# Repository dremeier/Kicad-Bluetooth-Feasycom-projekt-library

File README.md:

# Kicad-Bluetooth-Feasycom-projekt-library
KiCad 7 Library for the FSC-BT1026 Module and schematic with FSC-BT1026 and PCM5102.
The Feasycom module is a fantastic choice!
It is easy to control via UART, I2C and has I2S Audio bus as well direct SPDIF per default so no deep programming is necessary.
The Documentation is perfect and you can have a cheap experimental Board in Arduino-UNO format.

hope it is usefull for someone, 
enjoiy!

[Example Bluetooth schematic](https://github.com/dremeier/Kicad-Bluetooth-Feasycom-projekt-library/blob/main/Bluetooth_FSC-BT1026x_project/Documents/Bluetooth_PCM5102_Circuit.pdf)
<object data="https://github.com/dremeier/Kicad-Bluetooth-Feasycom-projekt-library/blob/main/Bluetooth_FSC-BT1026x_project/Documents/Bluetooth_PCM5102_Circuit.pdf" type="application/pdf" width="100%">
</object>

## KiCad 3D-Package

## KiCad Projekt with the Feasycom Bluetooth Module (BMW-IbusTrx-Teensy)

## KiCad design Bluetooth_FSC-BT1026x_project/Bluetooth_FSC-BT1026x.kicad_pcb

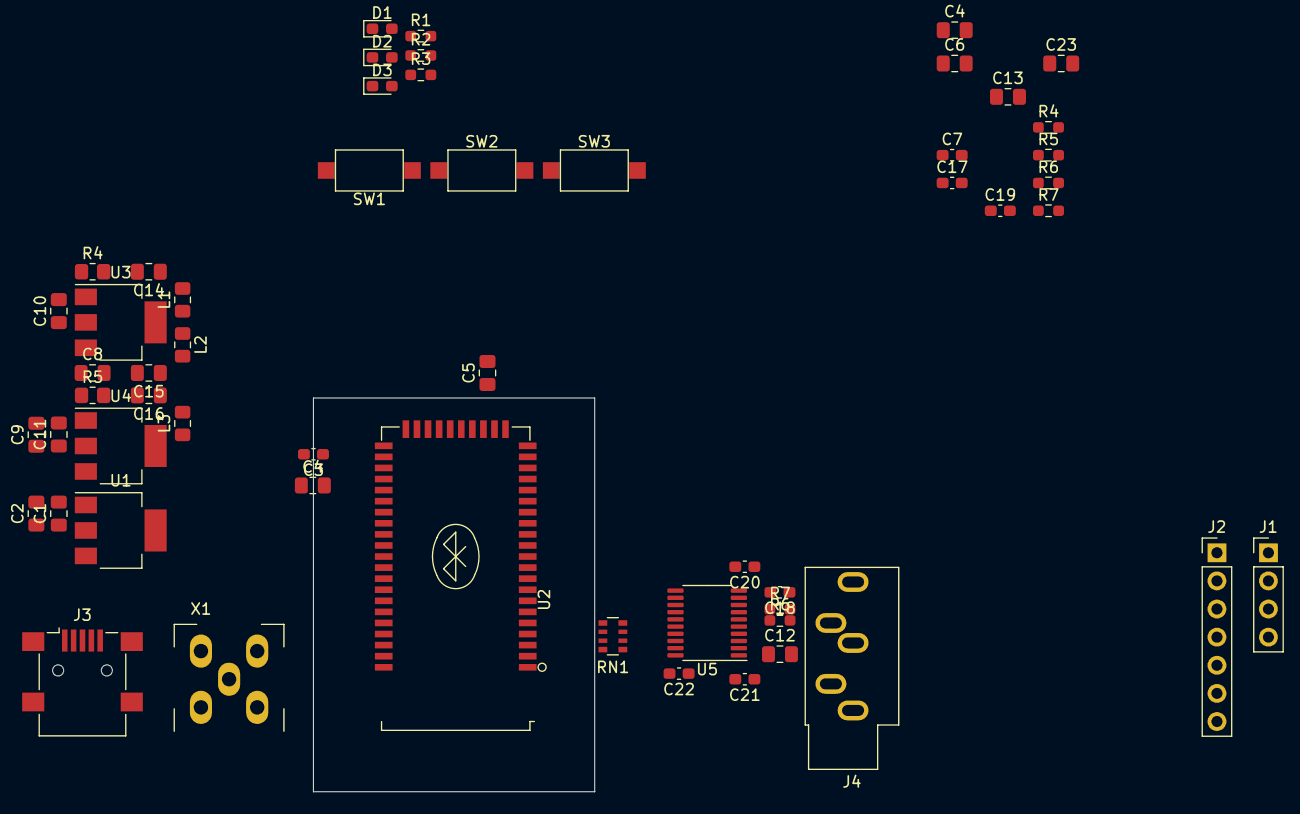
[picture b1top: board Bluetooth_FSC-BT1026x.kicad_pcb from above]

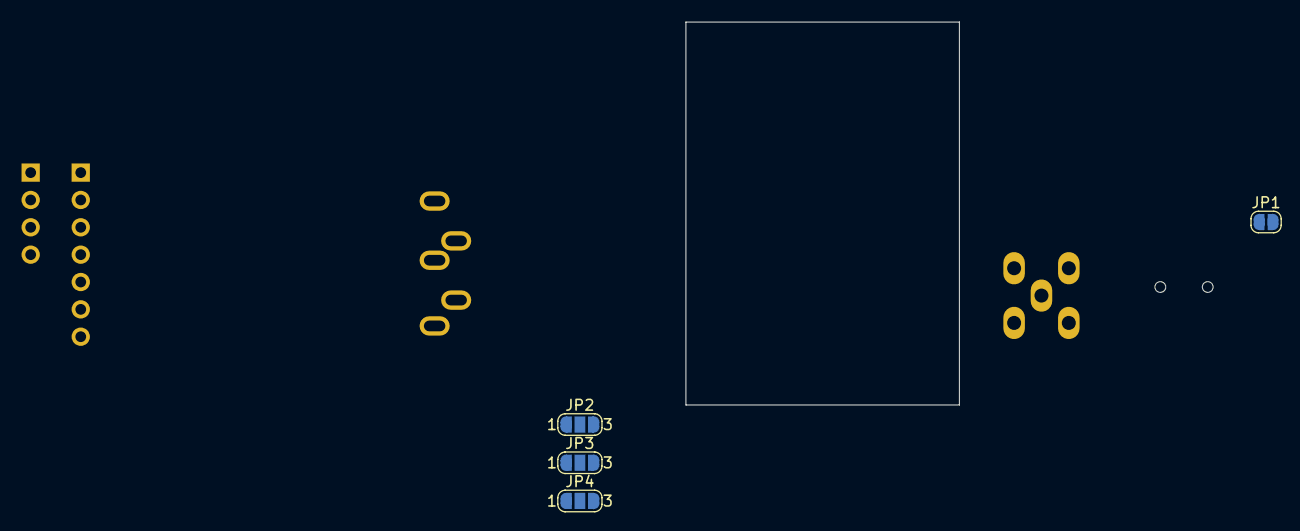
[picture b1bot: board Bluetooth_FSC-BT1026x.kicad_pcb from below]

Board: 2 copper layers, 59 parts (4 on the bottom side), 52 nets, no tracks yet.

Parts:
C1, C2, C14, C15, C16: 10μF; C_0805_2012Metric_Pad1.18x1.45mm_HandSolder
C3, C7, C17, C20, C21, C22: 100nF; C_0603_1608Metric_Pad1.08x0.95mm_HandSolder
C4, C4#2, C5, C6, C8, C9, C10, C11, C12, C13, C23: 2.2μF; C_0805_2012Metric_Pad1.18x1.45mm_HandSolder
C18, C19: 2.2nF; C_0603_1608Metric_Pad1.08x0.95mm_HandSolder
D1, D2, D3: LED; LED_0603_1608Metric_Pad1.05x0.95mm_HandSolder
J1: UART; PinHeader_1x04_P2.54mm_Vertical
J2: SPI; PinHeader_1x07_P2.54mm_Vertical
J3: USB_B_Mini; USB_Mini-B_Lumberg_2486_01_Horizontal
J4: line-out; Jack_3.5mm_CUI_SJ1-3535NG_Horizontal
JP1: USB-prog; SolderJumper-2_P1.3mm_Open_RoundedPad1.0x1.5mm
JP2: Latency; SolderJumper-3_P1.3mm_Open_RoundedPad1.0x1.5mm_NumberLabels
JP3: 44.1KHz; SolderJumper-3_P1.3mm_Open_RoundedPad1.0x1.5mm_NumberLabels
JP4: I²S; SolderJumper-3_P1.3mm_Open_RoundedPad1.0x1.5mm_NumberLabels
L1, L2, L3: 1μH; L_0805_2012Metric_Pad1.15x1.40mm_HandSolder
R1, R2, R3, R6#2, R7: 470; R_0603_1608Metric_Pad0.98x0.95mm_HandSolder
R4, R5, R6, R7#2: 22; R_0603_1608Metric_Pad0.98x0.95mm_HandSolder
R4#2, R5#2: 1; R_0805_2012Metric_Pad1.20x1.40mm_HandSolder
RN1: 22; R_Array_Convex_4x0603
SW1: next; SW_SPST_CK_RS282G05A3
SW2: back; SW_SPST_CK_RS282G05A3
SW3: Play/Power; SW_SPST_CK_RS282G05A3
U1: LT1117 CST-3.3; SOT-223-3_TabPin2
U2: FSC-BT1026E; FSC-BT1026x
U3, U4: ADP3339; SOT-223-3_TabPin2
U5: PCM5102; TSSOP-20_4.4x6.5mm_P0.65mm
X1: LTE; CONN_Fakra_DeLOCK_90°

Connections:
+3.3VP: C1.1, C2.1, C3.1, J2.2, SW1.1, SW2.1, SW3.1, U1.2 (VO), U2.33 (VBAT_IN)
+5VD: C8.1, C9.1, J1.1, J3.1 (VBUS), JP1.1 (A), U1.3 (VI), U3.3 (VI), U4.3 (VI)
/1.8V: C4.1, U2.35 (1.8V_OUT)
/BCK: R6.1, RN1.7 (R2.2), U2.4 (PCM_CLK/PI016)
/BT_3.3V: C5.1, C6.1, U2.31 (VDD_USB/3.3V_OUT), U2.36 (VDD_IO)
/BT_LED0: R1.2, U2.17 (AIO0/LED0)
/BT_LED1: R2.2, U2.18 (AIO1/LED1)
/BT_LED2: R3.2, U2.19 (AIO2/LED2)
/BT_back: SW2.2, U2.28 (PIO21)
/BT_mute: C7.1, U2.16 (BT_RTS/Pl02), U5.17 (XSMT)
/BT_next: SW1.2, U2.27 (PIO20)
/DIN: R5.1, RN1.6 (R3.2), U2.6 (PCM_OUT/PI018)
/LRCK: R4.1, RN1.5 (R4.2), U2.7 (PCM_SYNC/PIO17)
/SCK: R7#2.1, RN1.8 (R1.2)
/SPI_CLK: J2.5, U2.12 (PIO8)
/SPI_CSB: J2.6, U2.9 (PCM_MCLK_0UT/PI015)
/SPI_ENABLE: J2.3, U2.23 (PIO52)
/SPI_MISO: J2.7, U2.11 (PIO7)
/SPI_MOSI: J2.4, U2.10 (PIO6)
/USB_DN: J3.2 (D-), U2.38 (USB_DN)
/USB_DP: J3.3 (D+), U2.37 (USB_DP)
BT_CTRL: SW3.2, U2.34 (SYS_CTRL)
BT_RX: J1.2, U2.14 (BT_RX/PI04)
BT_Tx: J1.3, U2.13 (BT_TX/PI05)
GND: C1.2, C2.2, C3.2, C4.2, C4#2.1, C5.2, C6.2, D1.1 (K), D2.1 (K), D3.1 (K), J1.4, J2.1, J3.5 (GND), J3.6 (Shield), R4#2.1, R5#2.1, U1.1 (GND), U2.1 (GND), U2.22 (GND), U2.32 (GND), U2.50 (GND), U2.52 (GND), X1.2 (Ext)
GNDA: C8.2, C10.2, C13.2, C14.2, C15.2, C18.2, C19.2, C20.2, C21.2, J4.S, R4#2.2, U3.1 (GND), U5.3 (CPGND), U5.9 (AGND)
GNDD: C7.2, C9.2, C11.2, C16.2, C17.2, C22.2, C23.2, JP2.3 (B), JP3.3 (B), JP4.3 (B), R5#2.2, U4.1 (GND), U5.19 (DGND)
unnamed: C18.1, J4.R, R7.2
unnamed: C19.1, J4.T, R6#2.2
unnamed: D1.2 (A), R1.1
unnamed: D2.2 (A), R2.1
unnamed: D3.2 (A), R3.1
unnamed: JP1.2 (B), U2.39 (VCC_CHG)
unnamed: JP2.2 (C), U5.11 (FLT)
unnamed: JP3.2 (C), U5.10 (DEMP)
unnamed: JP4.2 (C), U5.16 (FMT)
unnamed: RN1.1 (R1.1), U5.12 (SCK)
unnamed: RN1.2 (R2.1), U5.13 (BCK)
unnamed: RN1.3 (R3.1), U5.14 (DIN)
unnamed: RN1.4 (R4.1), U5.15 (LRCK)
unnamed: U2.51 (RF_OUT), X1.1 (In)
unnamed: C10.1, L1.1, L2.1, U3.2 (VO)
unnamed: C11.1, L3.1, U4.2 (VO)
unnamed: C12.2, U5.4 (CAPM)
unnamed: C12.1, U5.2 (CAPP)
unnamed: C17.1, C23.1, U5.18 (LDOO)
unnamed: R6#2.1, U5.6 (OUTL)
unnamed: R7.1, U5.7 (OUTR)
unnamed: C13.1, U5.5 (VNEG)
VD: C15.1, C21.1, L2.2, U5.1 (CPVDD)
VDD: C16.1, C22.1, JP2.1 (A), JP3.1 (A), JP4.1 (A), L3.2, U5.20 (DVDD)
VDDA: C14.1, C20.1, L1.2, U5.8 (AVDD)

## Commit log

2023-12-15 Add 3D-package pic
